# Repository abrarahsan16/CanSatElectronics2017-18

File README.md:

# Ryerson International CanSat 2017-2018

This is the repository for Ryerson Team Tomahawk.

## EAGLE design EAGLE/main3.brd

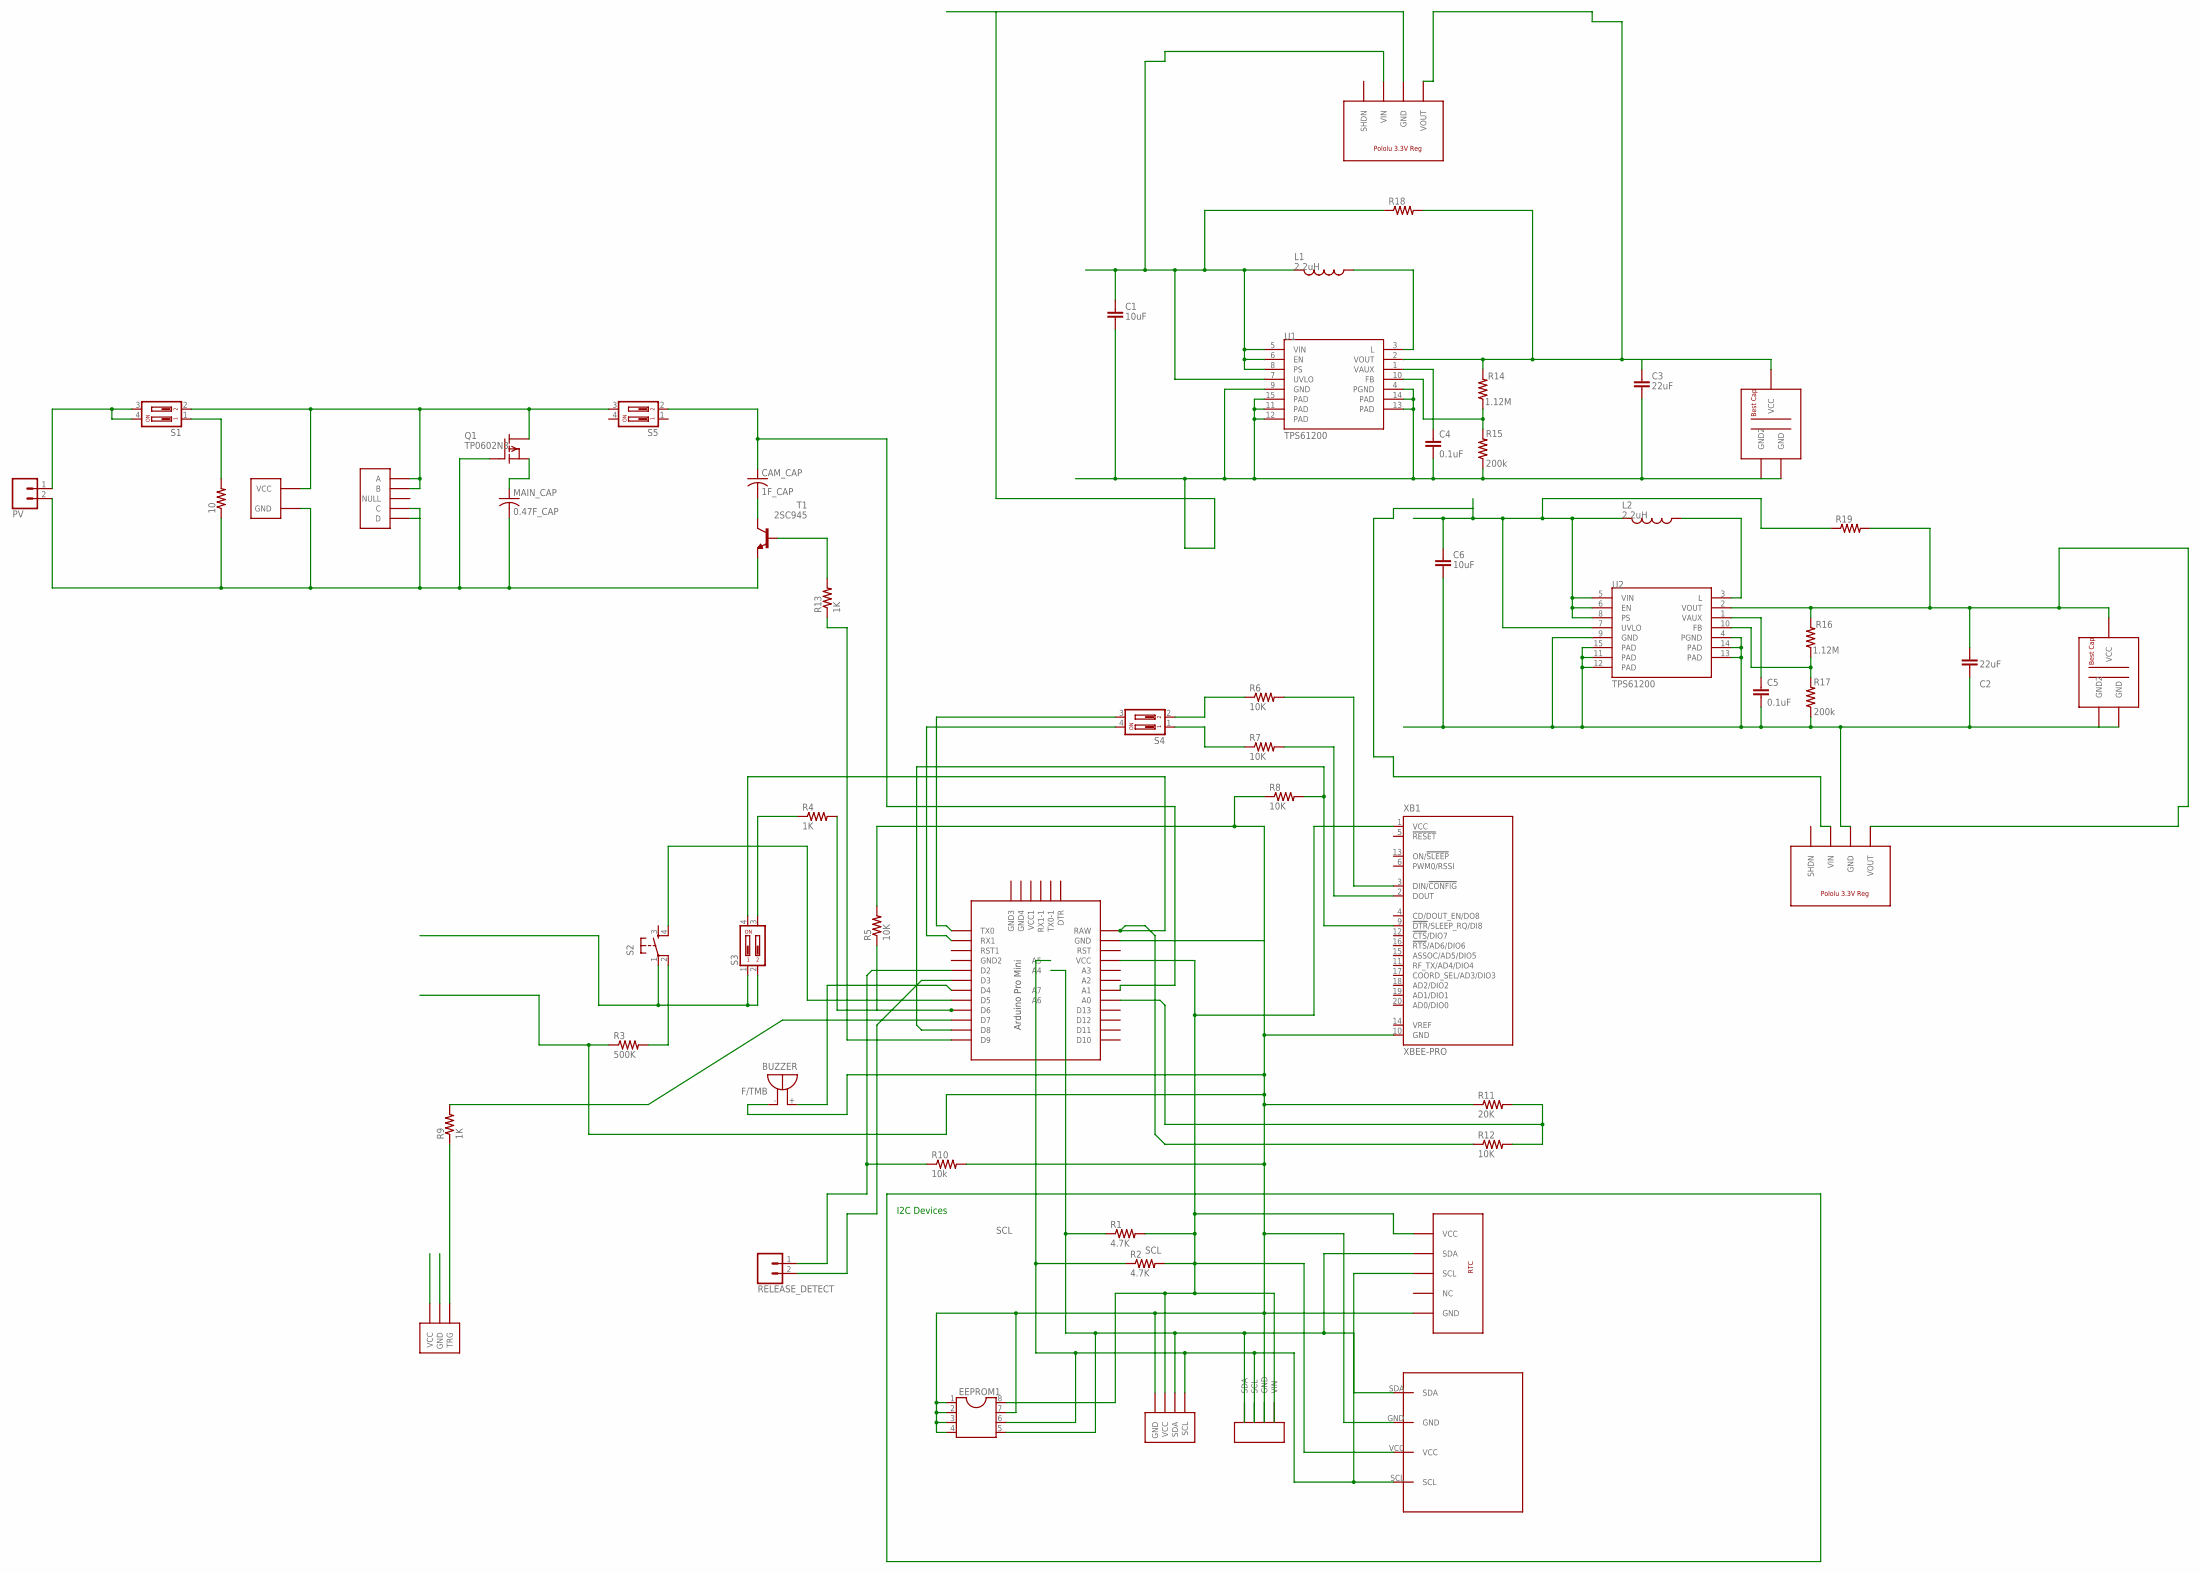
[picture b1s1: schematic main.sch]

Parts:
10: R-US_M1206; M1206
BUZZER: F/TMB
C1, C6: 10uF; 0805
C2, C3: 22uF; 0805
C4, C5: 0.1uF; 0805
CAM_CAP: 1F_CAP
EEPROM1: DIL8S; SOCKET-08
L1, L2: 2.2uH; 1212
MAIN_CAP: 0.47F_CAP
PITOTTUBE: SENSIRION; SENSIRIONSDP810
PV: CONN_02; 1X02
Q1: TP0602N3; TO-92
R1, R2: 4.7K; M0805
R3: 500K; M0805
R4, R13: 1K; M0805
R5: 10K; M0805
R6, R7, R8, R12: 10K; R0805
R9: 1K; R0805
R10: 10k; R0805
R11: 20K; R0805
R14, R16: 1.12M; 0805
R15, R17: 200k; 0805
R18: R-US_M0805; M0805
R19: R-US_R0805; R0805
RELEASE_DETECT: CONN_02; 1X02
S1, S3, S4, S5: DP02; DP-02
S2: TAC_SWITCHPTH; TACTILE-PTH
T1: 2SC945; TO92-ECB
U1, U2: TPS61200; QFN-10_PAD
U$1: PRO-MINI-2
U$2: HMC883L_BREAKOUT; HMC5833L_BREAKOUT
U$3: BMP180_BREAKOUT
U$4: CAMERA_BREAKOUT; CAMERA
U$5: EXT_PWR; EXTERNALPOWER
U$6: VOLTMETER
U$7: RTC
U$8, U$9: BESTCAP
U$10, U$11: POLOLU3VREG
XB1: XBEE-PRO

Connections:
CAM_VIN: C2.1, R16.2, R19.2, U2.2 (VOUT), U$4.VCC, U$9.VCC, U$11.VOUT
CAP_VIN: C6.1, CAM_CAP.+, L2.P$2 (2), R19.1, S5.2, U2.5 (VIN), U2.6 (EN), U2.7 (UVLO), U2.8 (PS), U$1.A1, U$11.VIN
FB: R14.1, R15.2, U1.10 (FB)
FB1: R16.1, R17.2, U2.10 (FB)
GND: 10.1, BUZZER.-, C1.2, C2.2, C3.2, C4.2, C5.2, C6.2, EEPROM1.1, EEPROM1.2, EEPROM1.3, EEPROM1.4, EEPROM1.7, MAIN_CAP.-, PITOTTUBE.GND, PV.2, Q1.2 (G), R3.1, R5.2, R8.1, R10.2, R11.1, R15.1, R17.1, T1.E, U1.4 (PGND), U1.9 (GND), U1.11 (PAD), U1.12 (PAD), U1.13 (PAD), U1.14 (PAD), U1.15 (PAD), U2.4 (PGND), U2.9 (GND), U2.11 (PAD), U2.12 (PAD), U2.13 (PAD), U2.14 (PAD), U2.15 (PAD), U$1.GND, U$2.GND, U$3.GND, U$4.GND, U$5.GND, U$6.C, U$6.D, U$7.GND, U$8.GND, U$8.GND2, U$9.GND, U$9.GND2, U$10.GND, U$11.GND, XB1.10 (GND)
MAIN_VIN: C3.1, R14.2, R18.2, S2.1, S3.1, S3.2, U1.2 (VOUT), U$8.VCC, U$10.VOUT
unnamed: L2.P$1 (1), U2.3 (L)
unnamed: C5.1, U2.1 (VAUX)
unnamed: R3.2, S2.2
unnamed: CAM_CAP.-, T1.C
unnamed: S2.4, U$1.D5
unnamed: R12.1, S3.4, U$1.RAW
unnamed: R4.1, S3.3
unnamed: R4.2, R5.1, U$1.D6
unnamed: R6.2, XB1.3 (DIN/!CONFIG)
unnamed: R6.1, S4.2
unnamed: S4.3, U$1.TX0
unnamed: R7.1, S4.1
unnamed: R7.2, XB1.2 (DOUT)
unnamed: S4.4, U$1.RX1
unnamed: R8.2, U$1.D8, XB1.9 (!DTR!/SLEEP_RQ/DI8)
unnamed: R9.2, U$1.D7
unnamed: R9.1, U$4.TRG
unnamed: BUZZER.+, U$1.D4
unnamed: R10.1, RELEASE_DETECT.1, U$1.D2
unnamed: RELEASE_DETECT.2, U$1.D3
unnamed: R11.2, R12.2, U$1.A0
unnamed: PV.1, S1.3, S1.4
unnamed: 10.2, S1.1
unnamed: R13.2, T1.B
unnamed: R13.1, U$1.D9
unnamed: L1.P$1 (1), U1.3 (L)
unnamed: Q1.3 (D), S1.2, S5.3, U$5.VCC, U$6.A, U$6.B
unnamed: C4.1, U1.1 (VAUX)
SCL: EEPROM1.6, PITOTTUBE.SCL, R2.1, U$1.A5, U$2.SCL, U$3.SCL, U$7.SCL
SDA: EEPROM1.5, PITOTTUBE.SDA, R1.1, U$1.A4, U$2.SDA, U$3.SDA, U$7.SDA
V33: EEPROM1.8, PITOTTUBE.VCC, R1.2, R2.2, U$1.VCC, U$2.VCC, U$3.VIN, U$7.VCC, XB1.1 (VCC)
VIN: C1.1, L1.P$2 (2), MAIN_CAP.+, Q1.1 (S), R18.1, U1.5 (VIN), U1.6 (EN), U1.7 (UVLO), U1.8 (PS), U$10.VIN

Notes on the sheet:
I2C Devices

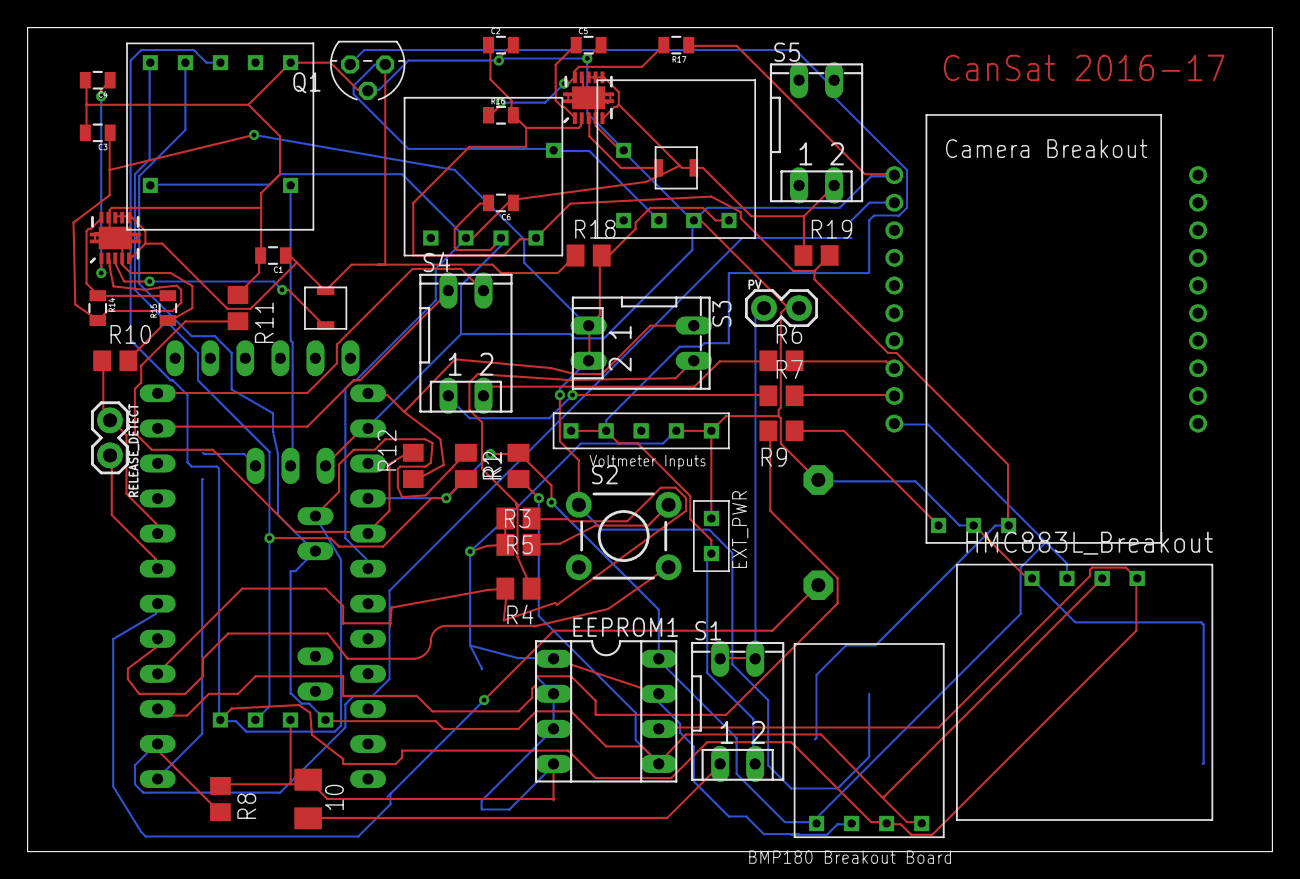
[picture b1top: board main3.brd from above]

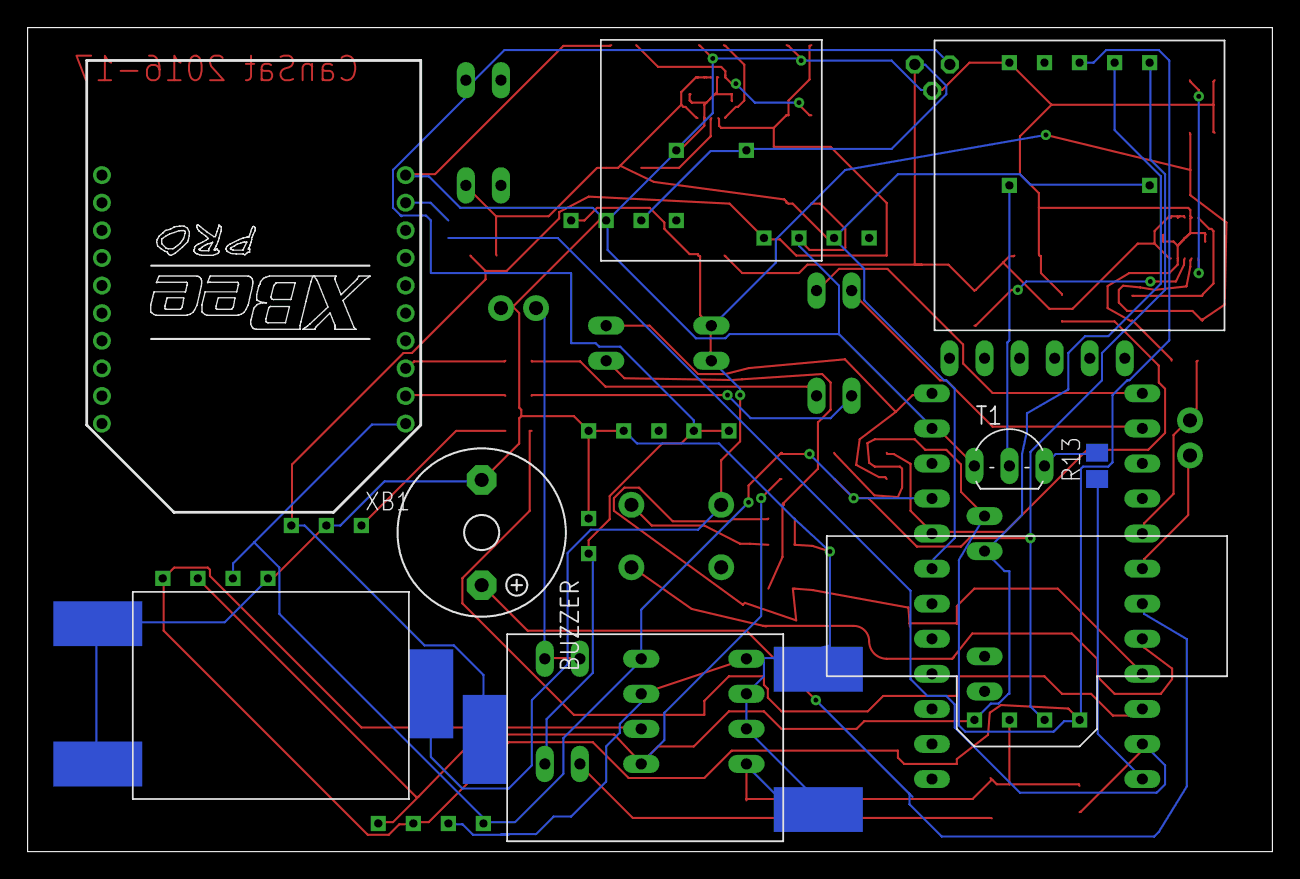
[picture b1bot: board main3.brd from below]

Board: 2 copper layers, 90.2 x 59.7 mm, 57 parts (9 on the bottom side), 38 nets.

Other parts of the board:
FRAME1: FRAME-LETTER; CREATIVE_COMMONS

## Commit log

2017-11-08 Past Years
2017-11-08 Voltmeter
2017-11-08 Create Droptest
2017-11-12 Rename Xbee_RTC_BMP.ino to Sensors/Xbee_RTC_BMP.ino
2017-11-12 continuous release mechanism
2017-11-14 delete
2017-11-21 Updated File
    Added HMC5883 in the code
2017-11-22 added voltage (still need tilt and gps)
2017-12-19 Added BMP Code
2018-01-23 From Andrew's Git
2018-01-23 ALL eagle files here
2018-01-23 Create 16-17 PCB
2018-01-23 Create GPS
2018-01-23 GPS code
2018-01-29 droptest
2018-02-05 Reorganized files
2018-02-06 adafuit mini spy camera camera
2018-02-24 Rearranging files
2018-02-24 Droptest V3
    Work in progress
2018-02-24 Drop Test V3
    Completed BMP, TILT, GPS.
    Flight staging incomplete. Radio incomplete, Camera incomplete.
    GPS requires test
2018-02-28 Updates
    Incomplete
2018-03-12 Camera
2018-03-12 Updated Camera
2018-03-12 Can delete Radio.ino
2018-03-13 Dont need
2018-03-13 Changes added for xbee test
2018-03-20 Ground Software V0.1
    -Updated mock Telemetry to current version
    -Updated update gui graph to current specifications (16 values)
    -Updated GUI to current specifications
    -Created a backup of previous ground software for reference
    TODO:
    -Figure out tableHandling
2018-03-20 .
    .
2018-03-21 Buzzer update
2018-03-26 Power Test V2
2018-03-26 GS V0.1
    -Updated mock Telemetry to current version
    -Updated update gui graph to current specifications (16 values)
    -Updated GUI to current specifications
    TODO:
    -Figure out tableHandling
    -Testing
2018-03-29 GPS BAUD RATE
    Updated GPS baud rate to 9600 for testing purposes.
2018-03-29 Revert "GPS BAUD RATE"
    This reverts commit a0b1d49e9fb502d09399c8fab6b7c793ce339c34.
2018-03-29 New line
2018-03-31 Ground Software V1.0
    -Data now prints to table and is being plotted
    -Everything seems to work
    Possible TODO:
    - Add message for when deployed!
2018-04-03 GS V1.1
    Made several updates to GUI
    - Updated logo, team ID and moved top left elements to look more
    pleasing
    - Added software state button that changes colour based on current state
    - Updated comments to better explain tableHandling
2018-04-03 Minor fixes
    Fixed current state button
2018-04-03 Removing gui graph to fix github issue
2018-04-03 Fixed GUIgraph
2018-04-03 Fixed update_GUIgraph
2018-05-02 EEPROM changes
2018-05-05 Small Update
2018-05-08 DropTest_V4
2018-05-29 Added SI units to GUI

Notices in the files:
parts and their libraries:
SparkFun-Retired: Licensing: Creative Commons ShareAlike 4.0 International - https://creativecommons.org/licenses/by-sa/4.0
SparkFun-Aesthetics: Released under the Creative Commons Attribution Share-Alike 4.0 License
SparkFun-Aesthetics: https://creativecommons.org/licenses/by-sa/4.0
